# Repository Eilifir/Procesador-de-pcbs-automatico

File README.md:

# Procesador-de-pcbs-automatico
Placas + diseño 3d de un proyecto de procesado de pcb

Este fue un proyecto hecho en 2020 entre tres personas, yo cuelgo mi parte que fue la programacion y diseño de placas las cuales fueron hechas en Altium, el diseñado 3d fue hecho por mis compañeros del proyecto

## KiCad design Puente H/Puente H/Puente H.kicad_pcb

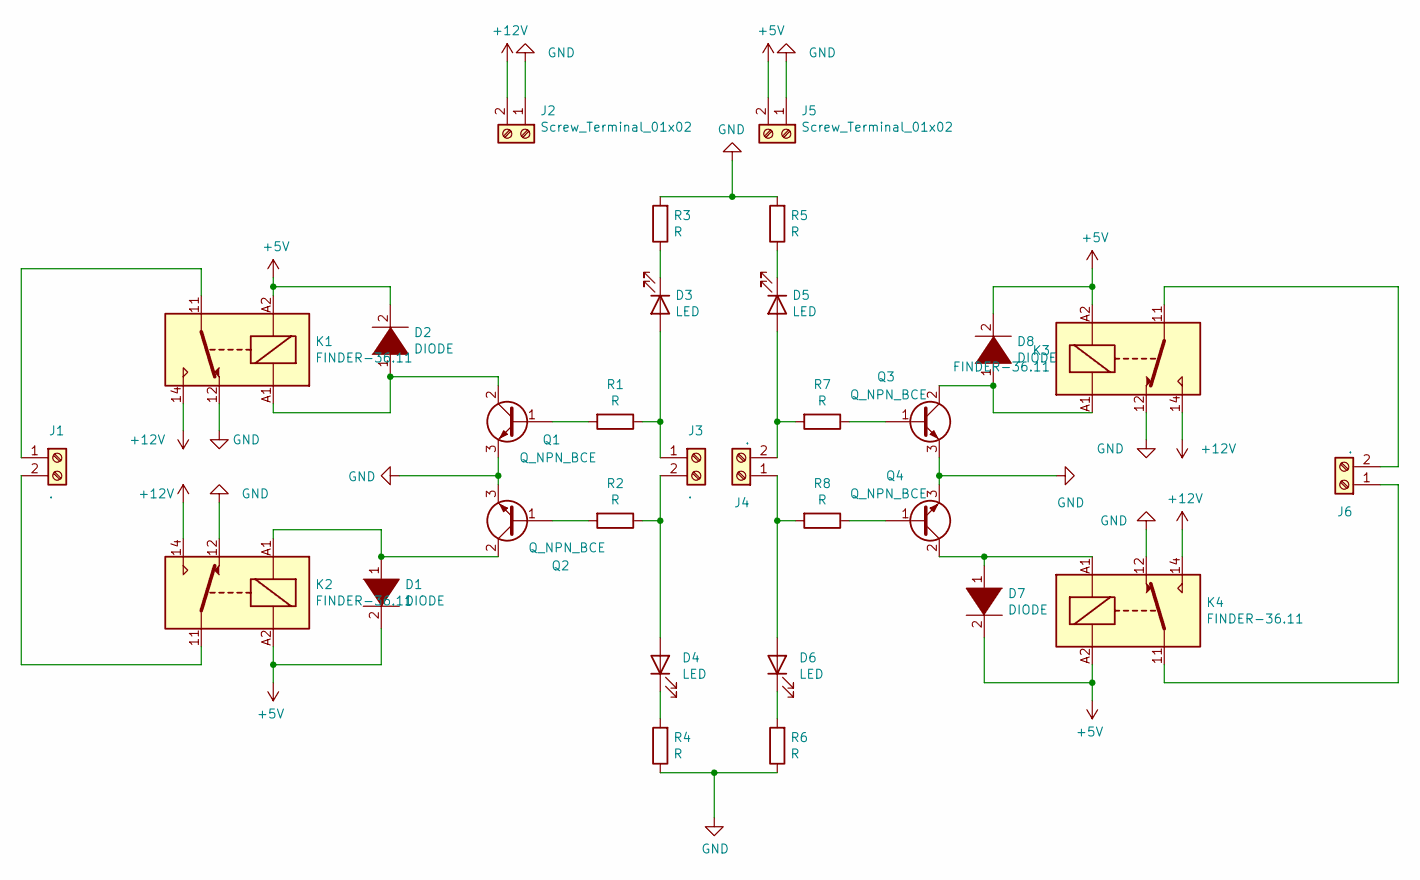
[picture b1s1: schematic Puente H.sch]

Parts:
D1, D2, D7, D8: DIODE; D_A-405_P10.16mm_Horizontal
D3, D4, D5, D6: LED; LED_D1.8mm_W3.3mm_H2.4mm
J1, J3, J4, J6: .; TerminalBlock_Altech_AK300-2_P5.00mm
J2, J5: Screw_Terminal_01x02; TerminalBlock_Altech_AK300-2_P5.00mm
K1, K2, K3, K4: FINDER-36.11; Relay_SPDT_Finder_36.11
Q1, Q2, Q3, Q4: Q_NPN_BCE; SIPAK_Vertical
R1, R2, R3, R4, R5, R6, R7, R8: R; R_Axial_DIN0309_L9.0mm_D3.2mm_P12.70mm_Horizontal

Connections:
+5V: D1.2 (A), D2.2 (A), D7.2 (A), D8.2 (A), J5.2, K1.A2, K2.A2, K3.A2, K4.A2
+12V: J2.2, K1.14, K2.14, K3.14, K4.14
GND: J2.1, J5.1, K1.12, K2.12, K3.12, K4.12, Q1.3 (E), Q2.3 (E), Q3.3 (E), Q4.3 (E), R3.2, R4.1, R5.2, R6.1
unnamed: D1.1 (K), K2.A1, Q2.2 (C)
unnamed: D2.1 (K), K1.A1, Q1.2 (C)
unnamed: D3.1 (K), R3.1
unnamed: D3.2 (A), J3.1, R1.1
unnamed: D4.1 (K), R4.2
unnamed: D4.2 (A), J3.2, R2.1
unnamed: D5.1 (K), R5.1
unnamed: D5.2 (A), J4.2, R7.2
unnamed: D6.1 (K), R6.2
unnamed: D6.2 (A), J4.1, R8.2
unnamed: D7.1 (K), K4.A1, Q4.2 (C)
unnamed: D8.1 (K), K3.A1, Q3.2 (C)
unnamed: J1.1, K1.11
unnamed: J1.2, K2.11
unnamed: J6.1, K4.11
unnamed: J6.2, K3.11
unnamed: Q1.1 (B), R1.2
unnamed: Q2.1 (B), R2.2
unnamed: Q3.1 (B), R7.1
unnamed: Q4.1 (B), R8.1

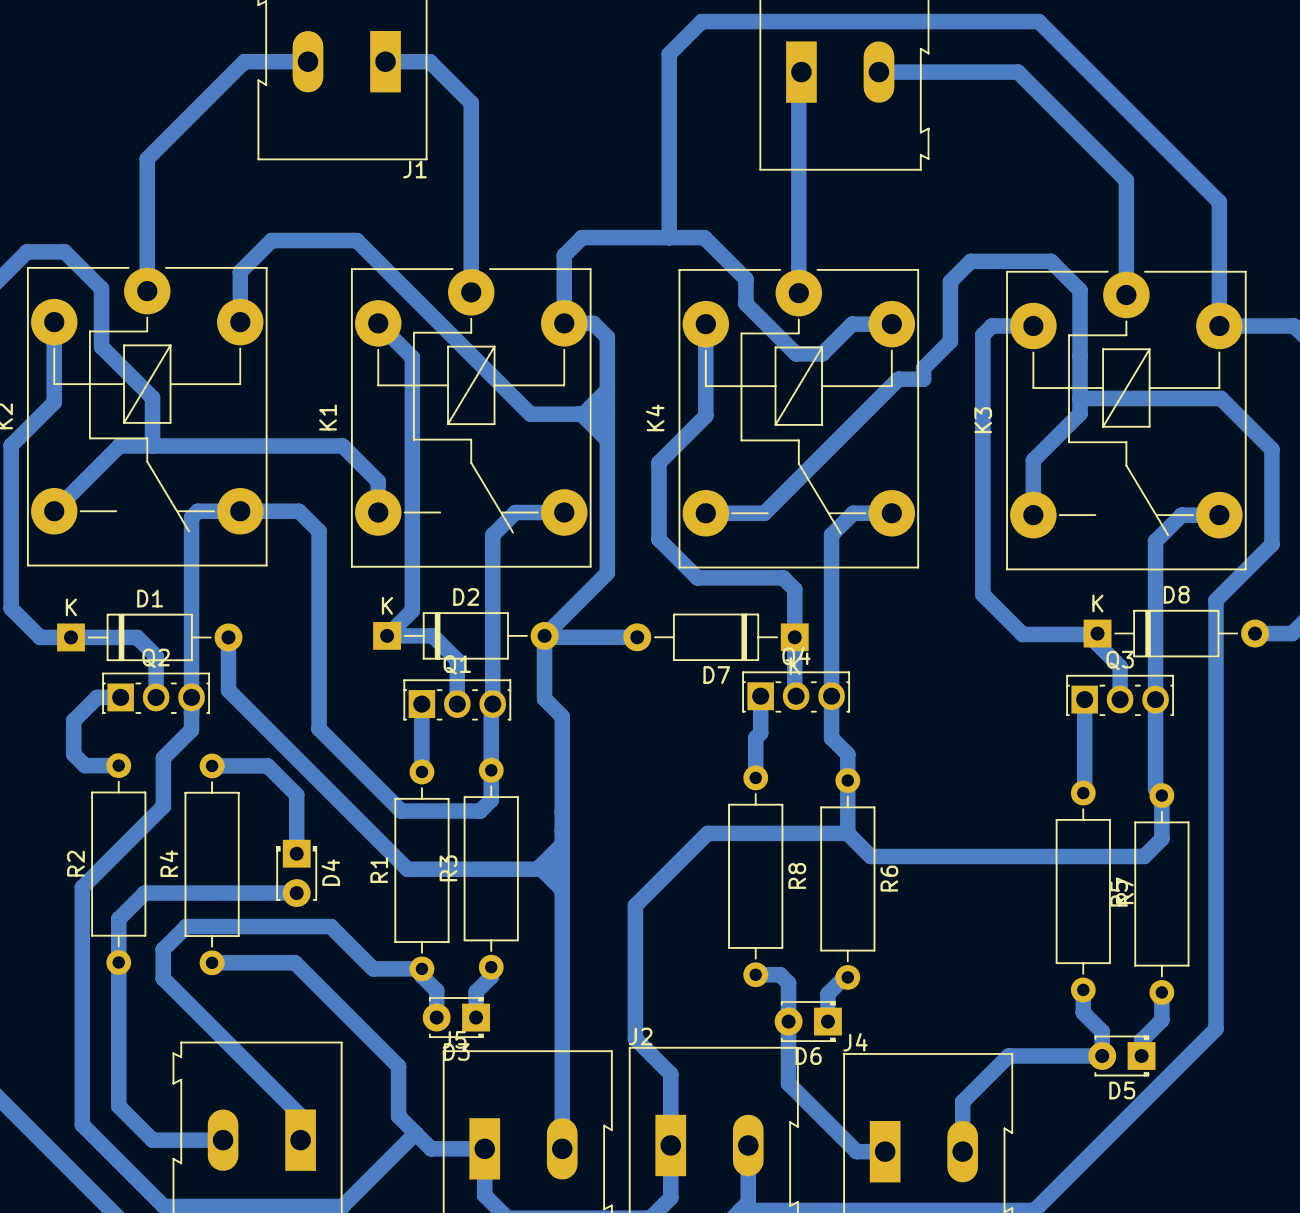
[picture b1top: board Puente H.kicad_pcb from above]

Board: 2 copper layers, 30 parts (0 on the bottom side), 23 nets.

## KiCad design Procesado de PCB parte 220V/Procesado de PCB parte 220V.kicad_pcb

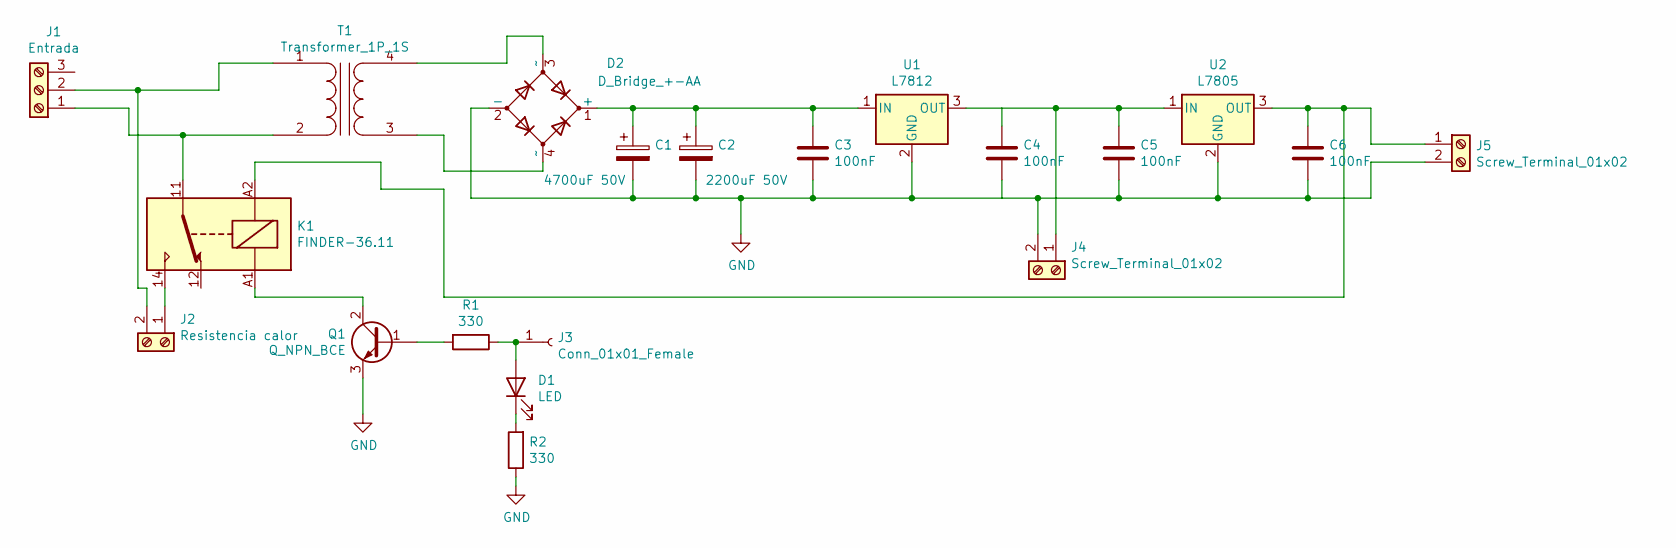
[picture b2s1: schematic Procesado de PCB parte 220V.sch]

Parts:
C1: 4700uF 50V; CP_Radial_D10.0mm_P2.50mm
C2: 2200uF 50V; CP_Radial_D10.0mm_P2.50mm
C3, C4, C5, C6: 100nF; C_Axial_L3.8mm_D2.6mm_P7.50mm_Horizontal
D1: LED; LED_D1.8mm_W1.8mm_H2.4mm_Horizontal_O6.35mm_Z1.6mm
D2: D_Bridge_+-AA; Diode_Bridge_19.0x3.5x10.0mm_P5.0mm
J1: Entrada; TerminalBlock_Altech_AK300-3_P5.00mm
J2: Resistencia calor; TerminalBlock_Altech_AK300-2_P5.00mm
J3: Conn_01x01_Female; Pin_D0.7mm_L6.5mm_W1.8mm_FlatFork
J4, J5: Screw_Terminal_01x02; TerminalBlock_Altech_AK300-2_P5.00mm
K1: FINDER-36.11; Relay_SPDT_Finder_36.11
Q1: Q_NPN_BCE; SIPAK_Vertical
R1, R2: 330; R_Axial_DIN0207_L6.3mm_D2.5mm_P10.16mm_Horizontal
T1: Transformer_1P_1S; Transformer_Toroid_Horizontal_D14.0mm_Amidon-T50
U1: L7812; TO-220-3_Vertical
U2: L7805; TO-220-3_Vertical

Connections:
GND: C1.2, C2.2, C3.2, C4.2, C5.2, C6.2, D2.2 (-), J4.2, J5.2, Q1.3 (E), R2.1, U1.2 (GND), U2.2 (GND)
unnamed: C1.1, C2.1, C3.1, D2.1 (+), U1.1 (IN)
unnamed: C4.1, C5.1, J4.1, U1.3 (OUT), U2.1 (IN)
unnamed: C6.1, J5.1, K1.A2, U2.3 (OUT)
unnamed: D1.1 (K), R2.2
unnamed: D1.2 (A), J3.1, R1.1
unnamed: D2.3 (~~), T1.4 (SB)
unnamed: D2.4 (~~), T1.3 (SA)
unnamed: J1.1, K1.11, T1.2 (AB)
unnamed: J1.2, J2.2, T1.1 (AA)
unnamed: J2.1, K1.14
unnamed: K1.A1, Q1.2 (C)
unnamed: Q1.1 (B), R1.2

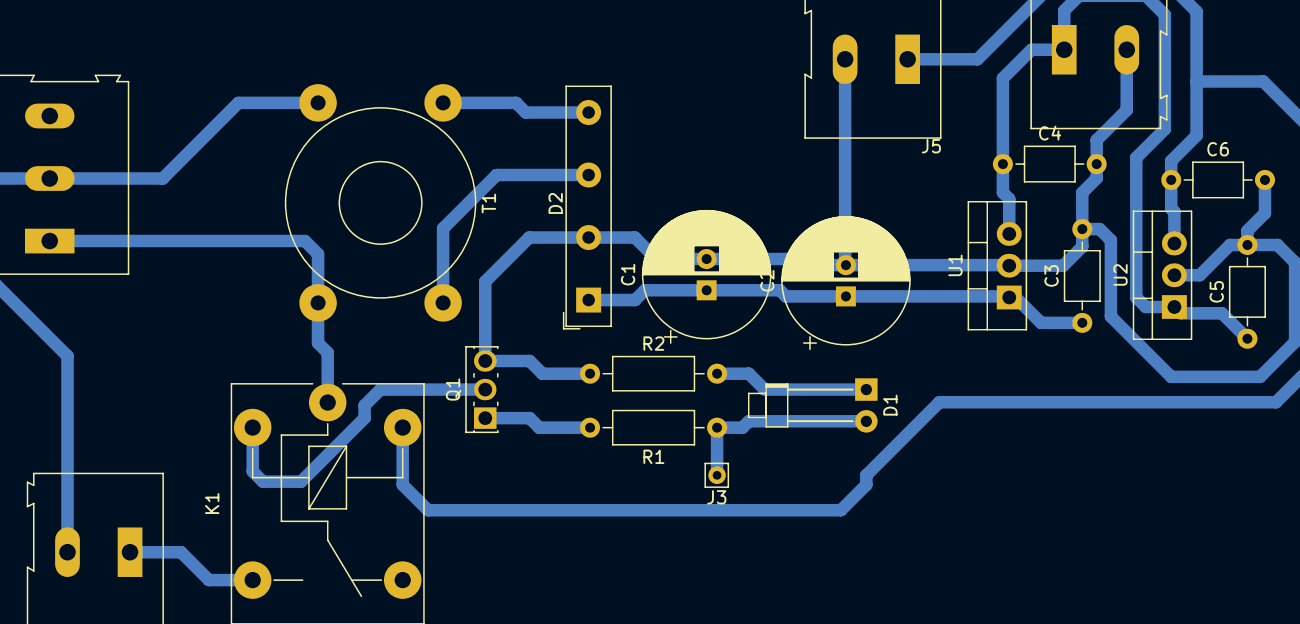
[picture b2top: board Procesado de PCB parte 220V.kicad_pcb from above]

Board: 2 copper layers, 20 parts (0 on the bottom side), 13 nets.
